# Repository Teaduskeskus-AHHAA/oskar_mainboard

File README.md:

# Oskar Mainboard

The AVR-based mainboard hardware and firmware for motor and other electronics control for AHHAA's newest robotic explainer - Oskar III. 

Hardware is currently being designed for the AVR2561, puerly for the benefit of having the most Program Memory available amongst the AVR-8 family. The software will compile to most other AVR-8 devices, prototyping has been done on an atmega328.

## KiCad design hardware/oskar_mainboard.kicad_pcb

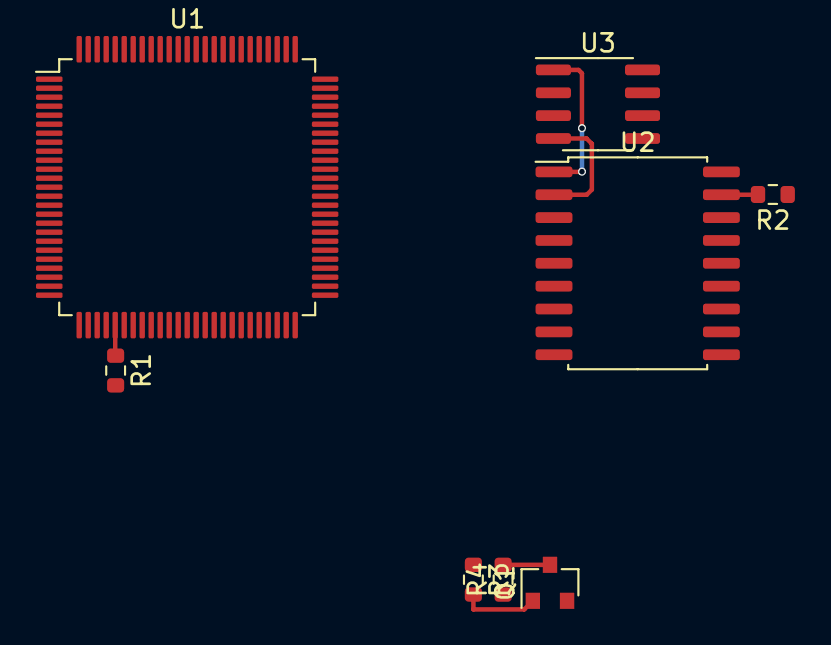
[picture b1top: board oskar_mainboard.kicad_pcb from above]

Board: 2 copper layers, 8 parts (0 on the bottom side), 9 nets.

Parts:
Q1: BC847; SOT-23
R1, R2, R4: 10k; R_0603_1608Metric
R3: 1.5k; R_0603_1608Metric
U1: ATmega2560-16AU; TQFP-100_14x14mm_P0.5mm
U2: MCP2515-xSO; SOIC-18W_7.5x11.6mm_P1.27mm
U3: MCP2551-I-SN; SOIC-8_3.9x4.9mm_P1.27mm

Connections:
+5V: R1.2, R2.1, R4.1
/RXCAN: U2.2, U3.4
/SBUS_IN: Q1.3, R4.2
/TXCAN: U2.1, U3.1
GND: Q1.2, U1.11, U1.32, U1.62, U1.81, U1.99
unnamed: Q1.1, R3.2
unnamed: R1.1, U1.30
unnamed: R2.2, U2.17
unnamed: U1.10, U1.31, U1.61, U1.80

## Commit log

2021-01-18 Add tthe 3 main IC's to the schematic
2021-01-19 Power connections and CAN crystal.
2021-01-19 Add Readme
2021-01-19 Clarify MCU selection and firmware targets in README.md.
2021-01-19 Re-add SPI and CAN Controller functionality.
2021-01-19 Revert "Re-add SPI and CAN Controller functionality."
    This reverts commit a3787ae60f74c41fc188f0dfc0dcf6d137fabc60.
2021-01-19 Remove build results
2021-01-19 Remove PN project file
2021-01-22 Begin making CAN interface library more robust and allow error checking.
2021-01-26 Pointer fixes and motor beginnings in controller firmware.
2021-02-03 Motors now able to zero themselves and restrict motion to preconfigured range.
2021-02-11 Add buttons for testing movement in range
2021-03-19 Functionalities to debug motor movements
2021-03-19 devel_prod: Rip out the motor key functionalities for prod code dev.
2021-03-22 devel_prod: Add an understanding of packets to the firmware.
2021-03-24 devel_prod: Add packet processing logic
2021-03-28 devel_prod: Send Odom back to computer
2021-04-04 devel_prod: Debug packets being all wrong
2021-04-04 devel_prod: make ros side segfault
2021-04-04 devel_prod: Verify breakage
2021-04-04 devel_prod: Init motor speed with conf
2021-04-04 Make state volatile
